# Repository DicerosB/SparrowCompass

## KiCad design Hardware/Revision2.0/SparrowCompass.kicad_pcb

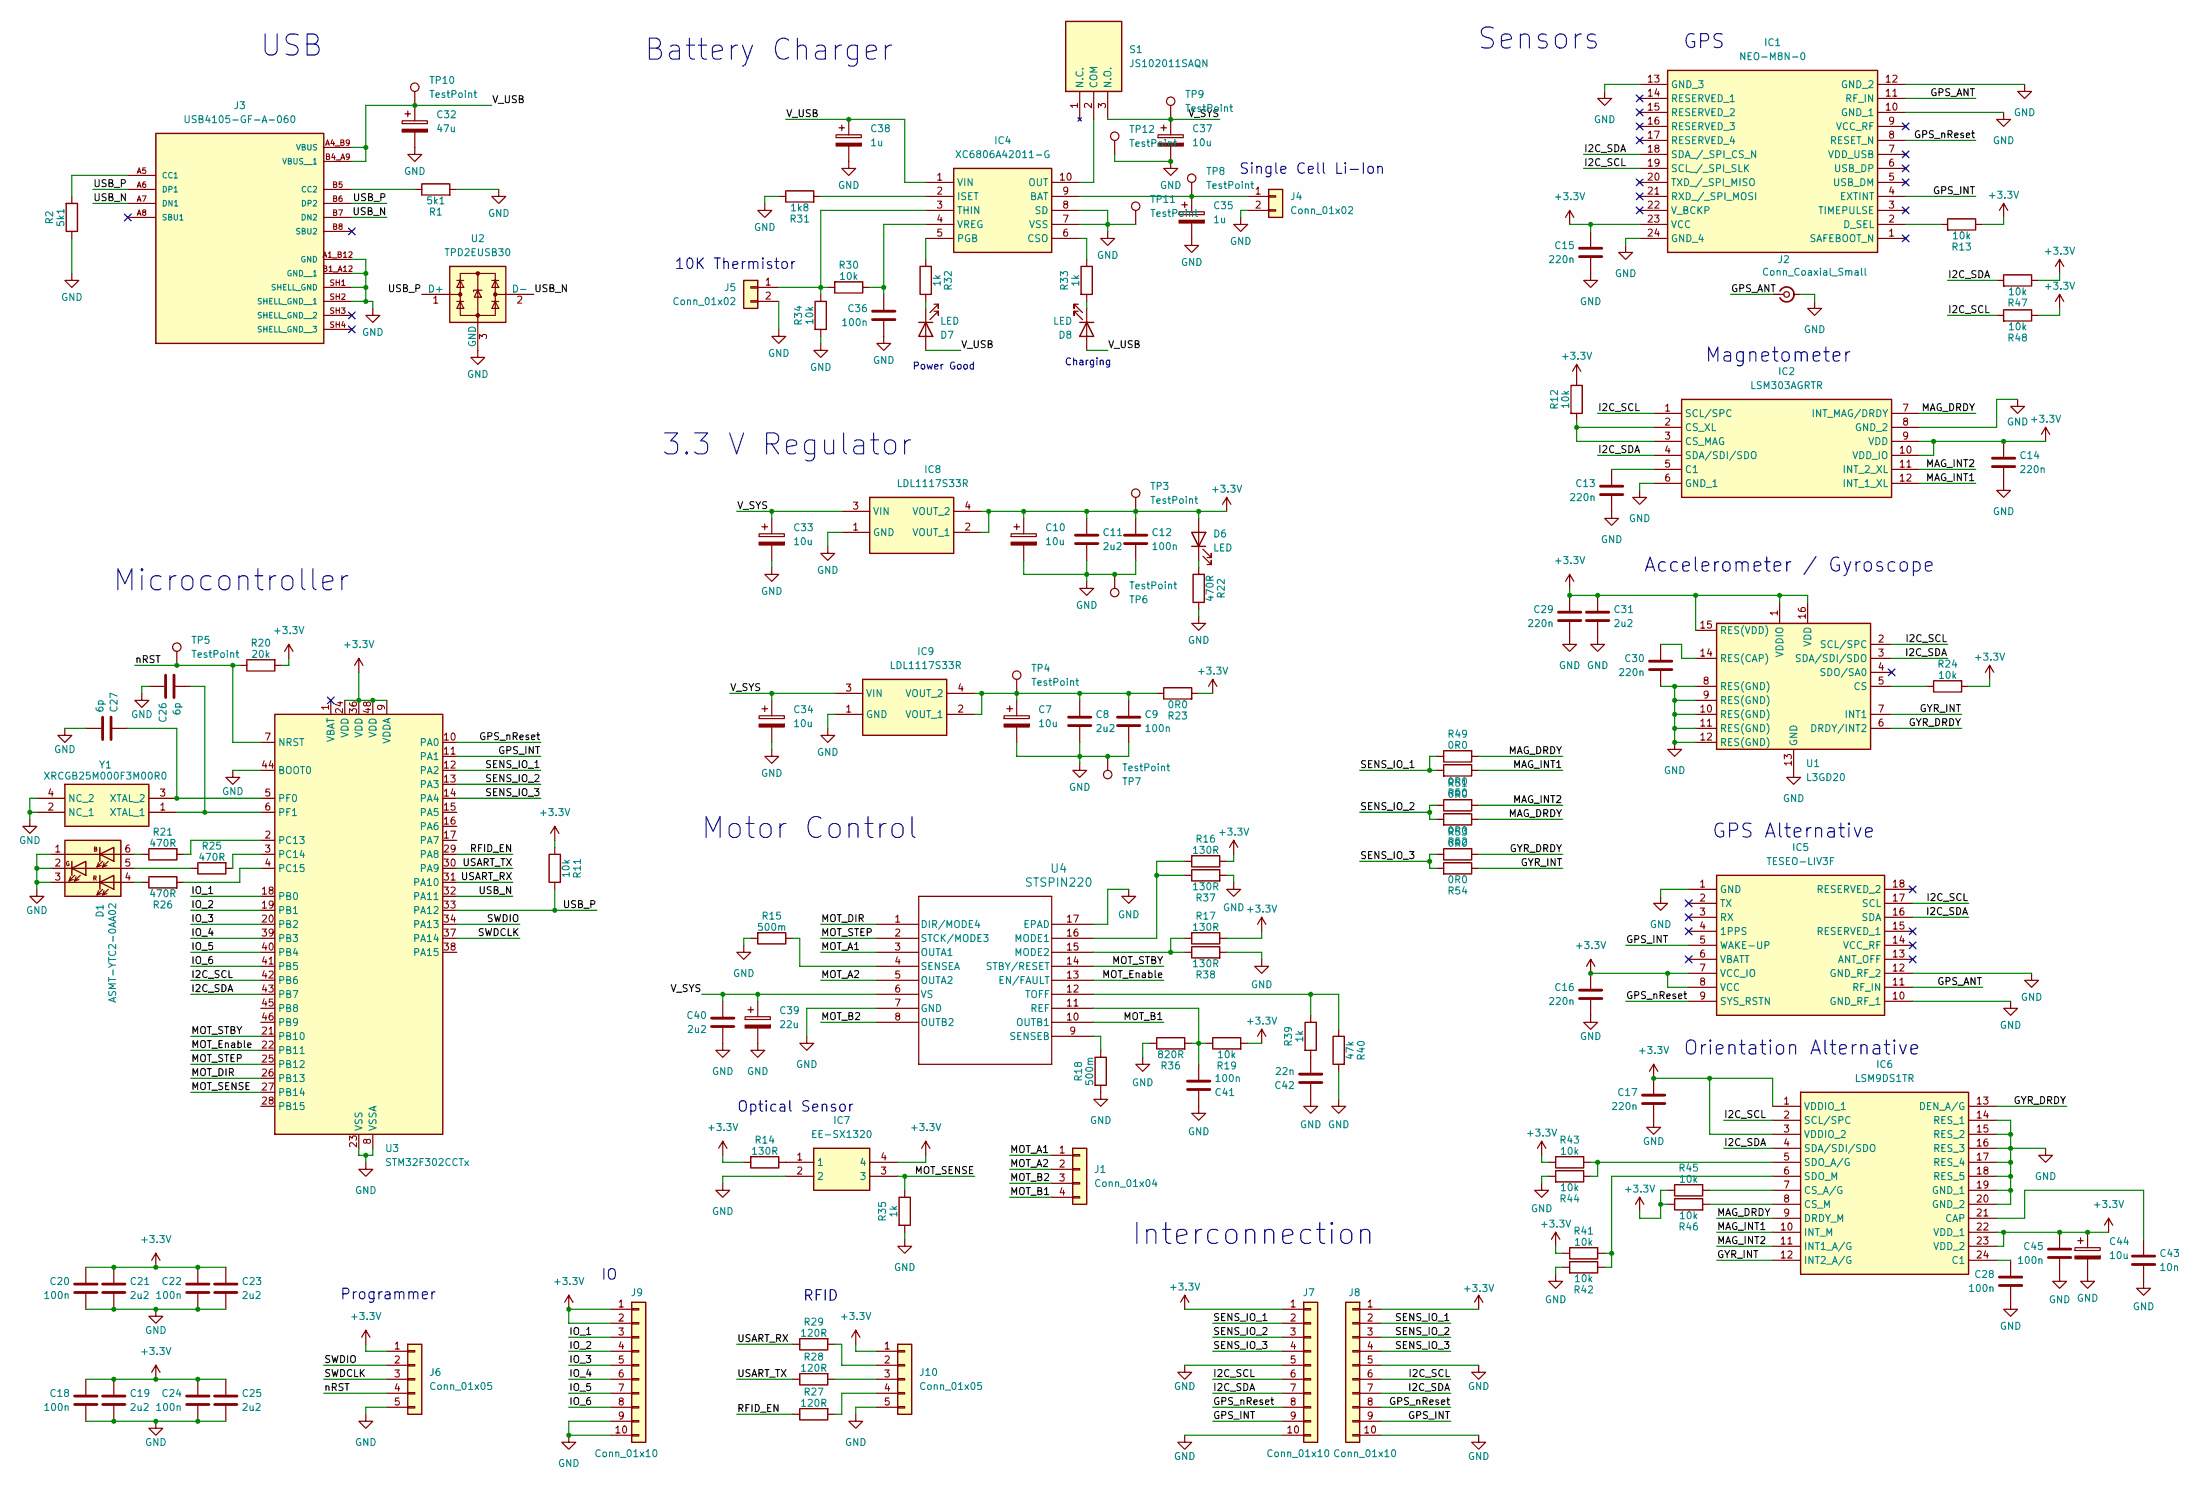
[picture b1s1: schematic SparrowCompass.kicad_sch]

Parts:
C7, C10, C33, C34, C37, C44: 10u; CP_EIA-6032-15_Kemet-U
C8, C11, C19, C21, C23, C25, C31, C40: 2u2; C_0603_1608Metric
C9, C12, C18, C20, C22, C24, C28, C36, C41, C45: 100n; C_0603_1608Metric
C13, C14, C15, C16, C17, C29, C30: 220n; C_0603_1608Metric
C26, C27: 6p; C_0603_1608Metric
C32: 47u; CP_EIA-6032-15_Kemet-U
C35, C38: 1u; CP_EIA-6032-15_Kemet-U
C39: 22u; CP_EIA-6032-15_Kemet-U
C42: 22n; C_0603_1608Metric
C43: 10n; C_0603_1608Metric
D1: ASMT-YTC2-0AA02; LED_Avago_PLCC6_3x2.8mm
D6, D7, D8: LED; LED_0603_1608Metric
IC1: NEO-M8N-0; NEO-M8T; Mouser Part Number 377-NEO-M8N-0
IC2: LSM303AGRTR; LGA-12; Mouser Part Number 511-LSM303AGRTR
IC4: XC6806A42011-G; XC6806A42011G; Manufacturer_Part_Number XC6806A42011-G
IC5: TESEO-LIV3F; SON110P970X1010X230-18N; Manufacturer_Part_Number TESEO-LIV3F
IC6: LSM9DS1TR; LGA-24L_3X3.5X1MM_; Manufacturer_Part_Number LSM9DS1TR
IC7: EE-SX1320; Mouser Part Number 653-EESX1320
IC8, IC9: LDL1117S33R; SOT230P700X180-4N; Manufacturer_Part_Number LDL1117S33R
J1: Conn_01x04; PinHeader_1x04_P2.54mm_Vertical
J2: Conn_Coaxial_Small; U.FL_Hirose_U.FL-R-SMT-1_Vertical
J3: USB4105-GF-A-060; GCT_USB4105-GF-A-060; PARTREV B3
J4, J5: Conn_01x02; PinHeader_1x02_P2.54mm_Vertical
J6, J10: Conn_01x05; PinHeader_1x05_P2.54mm_Vertical
J7, J8, J9: Conn_01x10; PinHeader_1x10_P1.27mm_Vertical
R1, R2: 5k1; R_0603_1608Metric
R11, R12, R13, R19, R24, R30, R34, R41, R42, R43, R44, R45, R46, R47, R48: 10k; R_0603_1608Metric
R14, R16, R17, R37, R38: 130R; R_0603_1608Metric
R15, R18: 500m; R_0603_1608Metric
R20: 20k; R_0603_1608Metric
R21, R22, R25, R26: 470R; R_0603_1608Metric
R23, R49, R50, R51, R52, R53, R54: 0R0; R_0603_1608Metric
R27, R28, R29: 120R; R_0603_1608Metric
R31: 1k8; R_0603_1608Metric
R32, R33, R35, R39: 1k; R_0603_1608Metric
R36: 820R; R_0603_1608Metric
R40: 47k; R_0603_1608Metric
S1: JS102011SAQN; Manufacturer_Part_Number JS102011SAQN
TP3, TP4, TP5, TP6, TP7, TP8, TP9, TP10, TP11, TP12: TestPoint; TestPoint_THTPad_D1.0mm_Drill0.5mm
U1: L3GD20; LGA-16_4x4mm_P0.65mm_LayoutBorder4x4y
U2: TPD2EUSB30; Texas_DRT-3
U3: STM32F302CCTx; LQFP-48_7x7mm_P0.5mm
U4: STSPIN220; VFQFPN-16_STM
Y1: XRCGB25M000F3M00R0; XRCGB; Mouser Part Number 81-XRCGB25M000F3M0R0

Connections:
+3.3V: C10.1, C11.1, C12.1, C14.1, C15.1, C16.1, C17.1, C18.1, C19.1, C20.1, C21.1, C22.1, C23.1, C24.1, C25.1, C29.1, C31.1, C44.1, C45.1, D6.2 (A), IC1.23 (VCC), IC2.9 (VDD), IC2.10 (VDD_IO), IC5.7 (VCC_IO), IC5.8 (VCC), IC6.1 (VDDIO_1), IC6.3 (VDDIO_2), IC6.22 (VDD_1), IC6.23 (VDD_2), IC7.4, IC8.2 (VOUT_1), IC8.4 (VOUT_2), J6.1, J7.1, J8.1, J9.1, J9.2, J10.1, R11.1, R12.1, R13.1, R14.2, R16.1, R17.1, R19.2, R20.2, R23.2, R24.2, R41.1, R43.1, R45.1, R46.1, R47.1, R48.1, TP3.1 (1_1), U1.1 (VDDIO), U1.15 (RES(VDD)), U1.16 (VDD), U3.9 (VDDA), U3.24 (VDD), U3.36 (VDD), U3.48 (VDD)
/GPS_ANT: IC1.11 (RF_IN), IC5.11 (RF_IN), J2.1 (In)
/GPS_INT: IC1.4 (EXTINT), IC5.5 (WAKE-UP), J7.9, J8.9, U3.11 (PA1)
/GPS_nReset: IC1.8 (RESET_N), IC5.9 (SYS_RSTN), J7.8, J8.8, U3.10 (PA0)
/GYR_DRDY: IC6.13 (DEN_A/G), R53.2, U1.6 (DRDY/INT2)
/GYR_INT: IC6.12 (INT2_A/G), R54.1, U1.7 (INT1)
/I2C_SCL: IC1.19 (SCL_/_SPI_SLK), IC2.1 (SCL/SPC), IC5.17 (SCL), IC6.2 (SCL/SPC), J7.6, J8.6, R48.2, U1.2 (SCL/SPC), U3.42 (PB6)
/I2C_SDA: IC1.18 (SDA_/_SPI_CS_N), IC2.4 (SDA/SDI/SDO), IC5.16 (SDA), IC6.4 (SDA/SDI/SDO), J7.7, J8.7, R47.2, U1.3 (SDA/SDI/SDO), U3.43 (PB7)
/IO_1: J9.3, U3.18 (PB0)
/IO_2: J9.4, U3.19 (PB1)
/IO_3: J9.5, U3.20 (PB2)
/IO_4: J9.6, U3.39 (PB3)
/IO_5: J9.7, U3.40 (PB4)
/IO_6: J9.8, U3.41 (PB5)
/MAG_DRDY: IC2.7 (INT_MAG/DRDY), IC6.9 (DRDY_M), R49.2, R52.1
/MAG_INT1: IC2.12 (INT_1_XL), IC6.10 (INT_M), R50.1
/MAG_INT2: IC2.11 (INT_2_XL), IC6.11 (INT1_A/G), R51.2
/MOT_A1: J1.1, U4.3 (OUTA1)
/MOT_A2: J1.2, U4.5 (OUTA2)
/MOT_B1: J1.4, U4.10 (OUTB1)
/MOT_B2: J1.3, U4.8 (OUTB2)
/MOT_DIR: U3.26 (PB13), U4.1 (DIR/MODE4)
/MOT_Enable: U3.22 (PB11), U4.13 (EN/FAULT)
/MOT_SENSE: IC7.3, R35.1, U3.27 (PB14)
/MOT_STBY: U3.21 (PB10), U4.14 (STBY/RESET)
/MOT_STEP: U3.25 (PB12), U4.2 (STCK/MODE3)
/RFID_EN: R27.1, U3.29 (PA8)
/SENS_IO_1: J7.2, J8.2, R49.1, R50.2, U3.12 (PA2)
/SENS_IO_2: J7.3, J8.3, R51.1, R52.2, U3.13 (PA3)
/SENS_IO_3: J7.4, J8.4, R53.1, R54.2, U3.14 (PA4)
/SWDCLK: J6.3, U3.37 (PA14)
/SWDIO: J6.2, U3.34 (PA13)
/USART_RX: R29.1, U3.31 (PA10)
/USART_TX: R28.1, U3.30 (PA9)
/USB_N: J3.A7 (DN1), J3.B7 (DN2), U2.2 (D-), U3.32 (PA11)
/USB_P: J3.A6 (DP1), J3.B6 (DP2), R11.2, U2.1 (D+), U3.33 (PA12)
/V_SYS: C33.1, C34.1, C37.1, C39.1, C40.1, IC8.3 (VIN), IC9.3 (VIN), S1.3 (N.O.), TP9.1 (1_1), U4.6 (VS)
/V_USB: C32.1, C38.1, D7.2 (A), D8.2 (A), IC4.1 (VIN), J3.A4_B9 (VBUS), J3.B4_A9 (VBUS__1), TP10.1 (1_1)
/nRST: J6.4, R20.1, TP5.1 (1_1), U3.7 (NRST)
GND: C7.2, C8.2, C9.2, C10.2, C11.2, C12.2, C13.2, C14.2, C15.2, C16.2, C17.2, C18.2, C19.2, C20.2, C21.2, C22.2, C23.2, C24.2, C25.2, C26.1, C27.2, C28.2, C29.2, C30.2, C31.2, C32.2, C33.2, C34.2, C35.2, C36.2, C37.2, C38.2, C39.2, C40.2, C41.1, C42.1, C43.2, C44.2, C45.2, D1.1 (KB), D1.2 (KG), D1.3 (KR), IC1.10 (GND_1), IC1.12 (GND_2), IC1.13 (GND_3), IC1.24 (GND_4), IC2.6 (GND_1), IC2.8 (GND_2), IC4.7 (VSS), IC4.8 (SD), IC5.1 (GND), IC5.10 (GND_RF_1), IC5.12 (GND_RF_2), IC6.14 (RES_1), IC6.15 (RES_2), IC6.16 (RES_3), IC6.17 (RES_4), IC6.18 (RES_5), IC6.19 (GND_1), IC6.20 (GND_2), IC7.2, IC8.1 (GND), IC9.1 (GND), J2.2 (Ext), J3.A1_B12 (GND), J3.B1_A12 (GND__1), J3.SH1 (SHELL_GND), J3.SH2 (SHELL_GND__1), J4.2, J5.2, J6.5, J7.5, J7.10, J8.5, J8.10, J9.9, J9.10, J10.5, R1.2, R2.1, R15.2, R18.2, R22.1, R31.1, R34.2, R35.2, R36.1, R37.2, R38.2, R40.2, R42.2, R44.2, TP6.1 (1_1), TP7.1 (1_1), TP11.1 (1_1), TP12.1 (1_1), U1.8 (RES(GND)), U1.9 (RES(GND)), U1.10 (RES(GND)), U1.11 (RES(GND)), U1.12 (RES(GND)), U1.13 (GND), U2.3 (GND), U3.8 (VSSA), U3.23 (VSS), U3.35 (VSS), U3.44 (BOOT0), U3.47 (VSS), U4.7 (GND), U4.17 (EPAD), Y1.2 (NC_1), Y1.4 (NC_2)
unnamed: C42.2, R39.2
unnamed: D1.6 (AB), R21.1
unnamed: D1.5 (AG), R25.1
unnamed: D1.4 (AR), R26.1
unnamed: D6.1 (K), R22.2
unnamed: D7.1 (K), R32.1
unnamed: D8.1 (K), R33.2
unnamed: IC1.2 (D_SEL), R13.2
unnamed: C13.1, IC2.5 (C1)
unnamed: IC2.2 (CS_XL), IC2.3 (CS_MAG), R12.2
unnamed: C35.1, IC4.9 (BAT), J4.1, TP8.1 (1_1)
unnamed: IC4.6 (CSO), R33.1
unnamed: IC4.2 (ISET), R31.2
unnamed: IC4.10 (OUT), S1.2 (COM)
unnamed: IC4.5 (PGB), R32.2
unnamed: IC4.3 (THIN), J5.1, R30.2, R34.1
unnamed: C36.1, IC4.4 (VREG), R30.1
unnamed: C28.1, IC6.24 (C1)
unnamed: C43.1, IC6.21 (CAP)
unnamed: IC6.7 (CS_A/G), R45.2
unnamed: IC6.8 (CS_M), R46.2
unnamed: IC6.5 (SDO_A/G), R43.2, R44.1
unnamed: IC6.6 (SDO_M), R41.2, R42.1
unnamed: IC7.1, R14.1
unnamed: C7.1, C8.1, C9.1, IC9.2 (VOUT_1), IC9.4 (VOUT_2), R23.1, TP4.1 (1_1)
unnamed: J3.A5 (CC1), R2.2
unnamed: J3.B5 (CC2), R1.1
unnamed: J10.2, R29.2
unnamed: J10.3, R28.2
unnamed: J10.4, R27.2
unnamed: R24.1, U1.5 (CS)
unnamed: C30.1, U1.14 (RES(CAP))
unnamed: R21.2, U3.2 (PC13)
unnamed: R25.2, U3.3 (PC14)
unnamed: R26.2, U3.4 (PC15)
unnamed: C27.1, U3.5 (PF0), Y1.3 (XTAL_2)
unnamed: C26.2, U3.6 (PF1), Y1.1 (XTAL_1)
unnamed: R16.2, R37.1, U4.16 (MODE1)
unnamed: R17.2, R38.1, U4.15 (MODE2)
unnamed: C41.2, R19.1, R36.2, U4.11 (REF)
unnamed: R15.1, U4.4 (SENSEA)
unnamed: R18.1, U4.9 (SENSEB)
unnamed: R39.1, R40.1, U4.12 (TOFF)

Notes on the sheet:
RFID
Optical Sensor
Battery Charger
3.3 V Regulator
Sensors
Charging
Single Cell Li-Ion
Orientation Alternative
10K Thermistor
GPS Alternative
Accelerometer / Gyroscope
Programmer
Motor Control
Microcontroller
Interconnection
Power Good
USB
Magnetometer
GPS

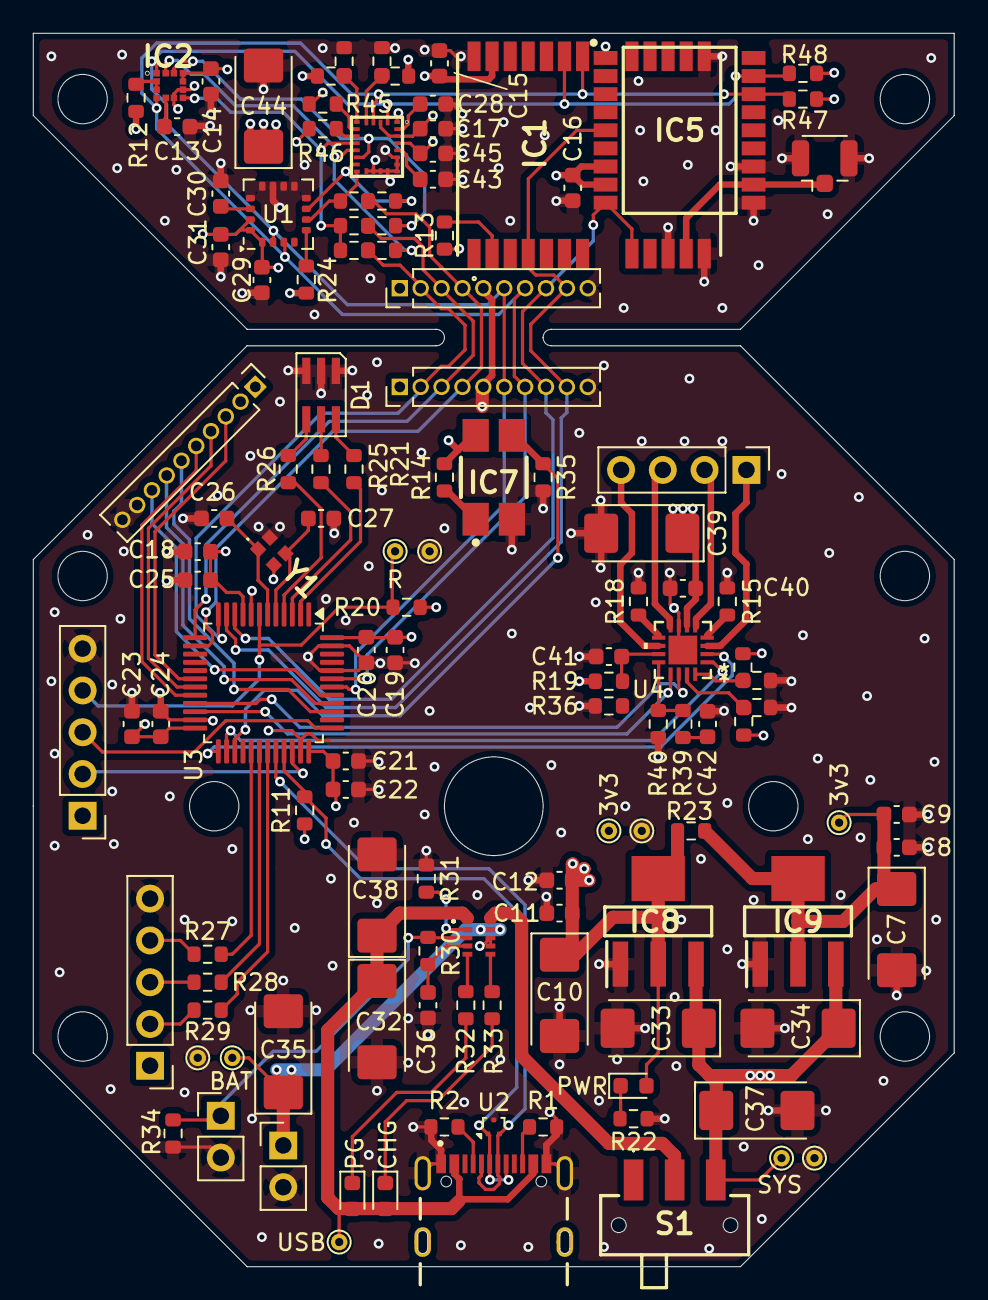
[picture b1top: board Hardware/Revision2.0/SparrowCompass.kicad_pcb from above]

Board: 4 copper layers, 56.0 x 75.0 mm, 123 parts (0 on the bottom side), 83 nets.

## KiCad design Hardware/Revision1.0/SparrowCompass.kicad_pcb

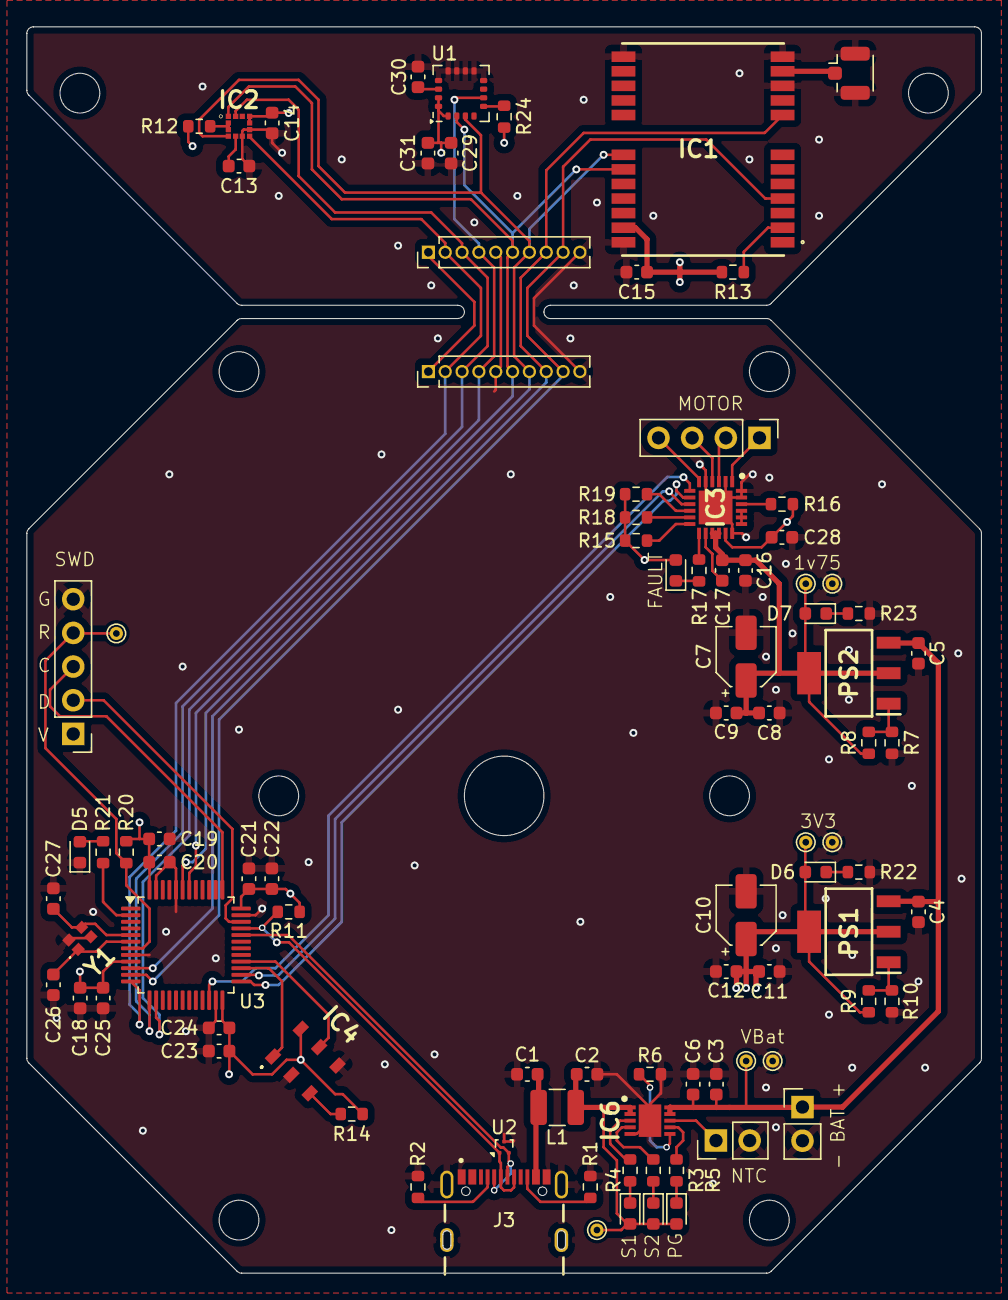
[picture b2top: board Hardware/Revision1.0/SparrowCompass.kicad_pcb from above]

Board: 4 copper layers, 72.0 x 94.0 mm, 90 parts (0 on the bottom side), 60 nets.

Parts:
C1, C2, C3, C6, C8, C11, C16, C19, C21, C23, C25, C31: 2u2; C_0603_1608Metric
C4, C5, C9, C12, C17, C18, C20, C22, C24, C28: 100n; C_0603_1608Metric
C7, C10: 10u; CP_Elec_4x5.3
C13, C14, C15, C29, C30: 220n; C_0603_1608Metric
C26, C27: 6p; C_0603_1608Metric
D1, D2, D3, D4, D5, D6, D7: LED; LED_0603_1608Metric
IC1: NEO-M8N-0; NEO-M8T
IC2: LSM303AGRTR; LGA-12
IC3: DRV8834RGER; QFN50P400X400X100-25N-D
IC4: AEDR-8300-1Q2; AEDR83001Q2
IC6: MCP73833T-AMI_MF; SON50P300X300X100-11N-D
J1: Conn_01x04; PinHeader_1x04_P2.54mm_Vertical
J2: Conn_Coaxial_Small; U.FL_Hirose_U.FL-R-SMT-1_Vertical
J3: USB4105-GF-A-060; GCT_USB4105-GF-A-060
J4, J5: Conn_01x02; PinHeader_1x02_P2.54mm_Vertical
J6: Conn_01x05; PinHeader_1x05_P2.54mm_Vertical
J7, J8: Conn_01x10; PinHeader_1x10_P1.27mm_Vertical
L1: 220R; L_1210_3225Metric
PS1, PS2: ZLDO1117QG33TA; SOT230P700X180-4N
R1, R2: 5k1; R_0603_1608Metric
R3, R4, R5, R14, R17, R21, R22, R23: 470R; R_0603_1608Metric
R6: 1k; R_0603_1608Metric
R7: 80R; R_0603_1608Metric
R8, R9: 200R; R_0603_1608Metric
R10: 330R; R_0603_1608Metric
R11, R12, R13, R15, R16, R18, R19, R24: 10k; R_0603_1608Metric
R20: 20k; R_0603_1608Metric
TP1, TP2, TP3, TP4, TP5, TP6, TP7, TP8: TestPoint; TestPoint_THTPad_D1.0mm_Drill0.5mm
U1: L3GD20; LGA-16_4x4mm_P0.65mm_LayoutBorder4x4y
U2: TPD2EUSB30; Texas_DRT-3
U3: STM32F302CCTx; LQFP-48_7x7mm_P0.5mm
Y1: XRCGB25M000F3M00R0; XRCGB

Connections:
+3.3V: C10.1, C11.1, C12.1, C14.1, C15.1, C18.1, C19.1, C20.1, C21.1, C22.1, C23.1, C24.1, C25.1, C28.1, C29.1, C31.1, D4.2 (A), D6.2 (A), IC1.23 (VCC), IC2.9 (VDD), IC2.10 (VDD_IO), IC3.17 (VINT), IC4.6 (VCC), J6.1, J7.1, J8.1, PS1.2 (VOUT_1), PS1.4 (VOUT_2), R9.2, R11.1, R12.1, R13.1, R14.2, R15.1, R16.1, R18.1, R19.1, R20.1, R24.2, TP3.1, U1.1 (VDDIO), U1.15 (RES(VDD)), U1.16 (VDD), U3.9 (VDDA), U3.24 (VDD), U3.36 (VDD), U3.48 (VDD)
/1V75: C7.1, C8.1, C9.1, C16.1, C17.1, D7.2 (A), IC3.15 (VM_1), IC3.16 (VM_2), PS2.2 (VOUT_1), PS2.4 (VOUT_2), R8.2, TP4.1
/GPS_INT: IC1.4 (EXTINT), J7.9, J8.9, U3.11 (PA1)
/GPS_nReset: IC1.8 (RESET_N), J7.8, J8.8, U3.10 (PA0)
/GYR_DRDY: J7.4, J8.4, U1.6 (DRDY/INT2), U3.14 (PA4)
/I2C_SCL: IC1.19 (SCL_/_SPI_SLK), IC2.1 (SCL/SPC), J7.6, J8.6, U1.2 (SCL/SPC), U3.42 (PB6)
/I2C_SDA: IC1.18 (SDA_/_SPI_CS_N), IC2.4 (SDA/SDI/SDO), J7.7, J8.7, U1.3 (SDA/SDI/SDO), U3.43 (PB7)
/MAG_DRDY: IC2.7 (INT_MAG/DRDY), J7.2, J8.2, U3.12 (PA2)
/MAG_INT1: IC2.12 (INT_1_XL), J7.3, J8.3, U3.13 (PA3)
/MOT_A1: IC3.1 (AOUT_1), J1.1
/MOT_A2: IC3.3 (AOUT_2), J1.2
/MOT_B1: IC3.6 (BOUT_1), J1.4
/MOT_B2: IC3.4 (BOUT_2), J1.3
/MOT_DIR: IC3.9 (DIR_/_BPHASE), U3.26 (PB13)
/MOT_SENS_A: IC4.5 (CH_A), U3.28 (PB15)
/MOT_SENS_B: IC4.1 (CH_B), U3.27 (PB14)
/MOT_STEP: IC3.8 (STEP_/_BENBL), U3.25 (PB12)
/MOT_nEnable: IC3.7 (NENBL_/_AENBL), U3.22 (PB11)
/SWDCLK: J6.3, U3.37 (PA14)
/SWDIO: J6.2, U3.34 (PA13)
/USB_N: J3.A7 (DN1), J3.B7 (DN2), U2.2 (D-), U3.32 (PA11)
/USB_P: J3.A6 (DP1), J3.B6 (DP2), R11.2, U2.1 (D+), U3.33 (PA12)
/V_BAT: C3.1, C4.1, C5.1, C6.1, IC6.9 (VBAT_1), IC6.10 (VBAT_2), J4.1, PS1.3 (VIN), PS2.3 (VIN), TP2.1
/V_USB: C2.1, D1.2 (A), D2.2 (A), D3.2 (A), IC6.1 (VDD_1), IC6.2 (VDD_2), L1.2, TP1.1
/nRST: J6.4, R20.2, TP5.1, U3.7 (NRST)
GND: C1.2, C2.2, C3.2, C4.2, C5.2, C6.2, C7.2, C8.2, C9.2, C10.2, C11.2, C12.2, C13.2, C14.2, C15.2, C16.2, C18.2, C19.2, C20.2, C21.2, C22.2, C23.2, C24.2, C25.2, C26.1, C27.2, C28.2, C29.2, C30.2, C31.2, D5.1 (K), IC1.10 (GND_1), IC1.12 (GND_2), IC1.13 (GND_3), IC1.24 (GND_4), IC2.6 (GND_1), IC2.8 (GND_2), IC3.2 (AISEN), IC3.5 (BISEN), IC3.18 (GND_1), IC3.23 (BDECAY), IC3.24 (ADECAY), IC3.25 (GND_2), IC4.2 (GND), IC4.4 (GND_), IC6.5 (VSS), IC6.11 (EP), J2.2 (Ext), J3.A1_B12 (GND), J3.B1_A12 (GND__1), J3.SH1 (SHELL_GND), J3.SH2 (SHELL_GND__1), J3.SH3 (SHELL_GND__2), J3.SH4 (SHELL_GND__3), J4.2, J5.2, J6.5, J7.5, J7.10, J8.5, J8.10, R1.1, R2.1, R6.2, R7.2, R10.2, R22.1, R23.1, TP6.1, TP7.1, TP8.1, U1.8 (RES(GND)), U1.9 (RES(GND)), U1.10 (RES(GND)), U1.11 (RES(GND)), U1.12 (RES(GND)), U1.13 (GND), U2.3 (GND), U3.8 (VSSA), U3.23 (VSS), U3.35 (VSS), U3.44 (BOOT0), U3.47 (VSS), Y1.2 (NC_1), Y1.4 (NC_2)
unnamed: D1.1 (K), R3.2
unnamed: D2.1 (K), R4.1
unnamed: D3.1 (K), R5.2
unnamed: D4.1 (K), R17.2
unnamed: D5.2 (A), R21.1
unnamed: D6.1 (K), R22.2
unnamed: D7.1 (K), R23.2
unnamed: IC1.2 (D_SEL), R13.2
unnamed: IC1.11 (RF_IN), J2.1 (In)
unnamed: C13.1, IC2.5 (C1)
unnamed: IC2.2 (CS_XL), IC2.3 (CS_MAG), R12.2
unnamed: IC3.19 (AVREF), IC3.20 (BVREF), IC3.21 (VREFO)
unnamed: IC3.12 (CONFIG), R15.2
unnamed: IC3.10 (M0_/_APHASE), R19.2
unnamed: IC3.11 (M1), R18.2
unnamed: IC3.13 (NFAULT), R17.1
unnamed: IC3.22 (NSLEEP), R16.2
unnamed: C17.2, IC3.14 (VCP)
unnamed: IC4.3 (VLED), R14.1
unnamed: IC6.6 (PROG), R6.1
unnamed: IC6.3 (STAT1), R3.1
unnamed: IC6.4 (STAT2), R4.2
unnamed: IC6.8 (THERM), J5.1
unnamed: IC6.7 (~PG(TE)), R5.1
unnamed: J3.A5 (CC1), R2.2
unnamed: J3.B5 (CC2), R1.2
unnamed: C1.1, J3.A4_B9 (VBUS), J3.B4_A9 (VBUS__1), L1.1
unnamed: PS1.1 (ADJ), R9.1, R10.1
unnamed: PS2.1 (ADJ), R7.1, R8.1
unnamed: R24.1, U1.5 (CS)
unnamed: C30.1, U1.14 (RES(CAP))
unnamed: R21.2, U3.2 (PC13)
unnamed: C27.1, U3.5 (PF0), Y1.3 (XTAL_2)
unnamed: C26.2, U3.6 (PF1), Y1.1 (XTAL_1)

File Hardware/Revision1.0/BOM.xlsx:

Reference | Qty | Value | DNP | Footprint | Datasheet | Cost | Link | total
C1;C2;C3;C6;C8;C11;C16;C19;C21;C23;C25;C31 | 12 | 2u2 |  | Capacitor_SMD:C_0603_1608Metric | ~ | 0.09 | https://www.mouser.de/ProductDetail/Murata-Electronics/GRM18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 | 1.08
C4;C5;C9;C12;C17;C18;C20;C22;C24;C28 | 10 | 100n |  | Capacitor_SMD:C_0603_1608Metric | ~ | 0.09 | https://www.mouser.de/ProductDetail/KEMET/C0603C104Z4VACTU?q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 | 0.89999999999999991
C7;C10 | 2 | 10u |  | Capacitor_SMD:CP_Elec_4x5.3 | ~ | 0.05 | https://www.mouser.de/ProductDetail/Knowles-Illinois-Capacit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 | 0.1
C13;C14;C15;C29;C30 | 5 | 220n |  | Capacitor_SMD:C_0603_1608Metric | ~ | 0.09 | https://www.mouser.de/ProductDetail/Murata-Electronics/GRM18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 | 0.44999999999999996
C26;C27 | 2 | 6p |  | Capacitor_SMD:C_0603_1608Metric | ~ | 0.09 | https://www.mouser.de/ProductDetail/Murata-Electronics/GCM18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 | 0.18
D1;D2;D3;D4;D5;D6;D7 | 7 | LED |  | LED_SMD:LED_0603_1608Metric | ~ | 0.15 | https://www.mouser.de/ProductDetail/Wurth-Elektronik/150060B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 | 1.05
IC1 | 1 | NEO-M8N-0 |  | NEO-M8N-0:NEO-M8T | https://www.u-blox.com/sites/default/files/NEO-M8-FW3_DataSh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 | 27.09 | https://www.mouser.de/ProductDetail/u-blox/NEO-M8N-0?qs=zW32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 | 27.09
IC2 | 1 | LSM303AGRTR |  | LSM303AGRTR:LGA-12 | http://www.st.com/content/ccc/resource/technical/document/da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 | 4 | https://www.mouser.de/ProductDetail/STMicroelectronics/LSM30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 | 4
IC3 | 1 | DRV8834RGER |  | DRV8834RGER:QFN50P400X400X100-25N-D | http://www.ti.com/lit/gpn/drv8834 | 2.35 | https://www.mouser.de/ProductDetail/Texas-Instruments/DRV883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 | 2.35
IC4 | 1 | AEDR-8300-1Q2 |  | AEDR-8300-1Q2:AEDR83001Q2 | https://www.digikey.ph/en/products/detail/broadcom-limited/A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 | 8.31 | https://www.mouser.de/ProductDetail/Broadcom-Avago/AEDR-8300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 | 8.31
IC6 | 1 | MCP73833T-AMI_MF |  | MCP73833T-AMI_MF:SON50P300X300X100-11N-D | https://datasheet.datasheetarchive.com/originals/distributor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 | 0.98 | https://www.mouser.de/ProductDetail/Microchip-Technology/MCP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 | 0.98
J2 | 1 | Conn_Coaxial_Small |  | Connector_Coaxial:U.FL_Hirose_U.FL-R-SMT-1_Vertical | ~ | 1.25 | https://www.mouser.de/ProductDetail/Hirose-Connector/U.FL-R-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 | 1.25
J3 | 1 | USB4105-GF-A-060 |  | USB4105_GF_A_060:GCT_USB4105-GF-A-060 |  | 0.67 | https://www.mouser.de/ProductDetail/GCT/USB4105-GF-A-060?qs=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 | 0.67
L1 | 1 | 220R |  | Inductor_SMD:L_1210_3225Metric | ~ | 3.06 | https://www.mouser.de/ProductDetail/Wurth-Elektronik/7687709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 | 3.06
PS1;PS2 | 2 | ZLDO1117QG33TA |  | ZLDO1117QG33TA:SOT230P700X180-4N | https://www.diodes.com//assets/Datasheets/products_inactive_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 | 0.46 | https://www.mouser.de/ProductDetail/Diodes-Incorporated/ZLDO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 | 0.92
R1;R2 | 2 | 5k1 |  | Resistor_SMD:R_0603_1608Metric | ~ | 0.09 | https://www.mouser.de/ProductDetail/Vishay/CRCW06035K11FKEA?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 | 0.18
R3;R4;R5;R14;R17;R21;R22;R23 | 8 | 470R |  | Resistor_SMD:R_0603_1608Metric | ~ | 0.09 |  | 0.72
R6 | 1 | 1k |  | Resistor_SMD:R_0603_1608Metric | ~ | 0.09 |  | 0.09
R7 | 1 | 80R |  | Resistor_SMD:R_0603_1608Metric | ~ | 0.09 |  | 0.09
R8;R9 | 2 | 200R |  | Resistor_SMD:R_0603_1608Metric | ~ | 0.09 |  | 0.18
R10 | 1 | 330R |  | Resistor_SMD:R_0603_1608Metric | ~ | 0.09 |  | 0.09
R11;R12;R13;R15;R16;R18;R19;R24 | 8 | 10k |  | Resistor_SMD:R_0603_1608Metric | ~ | 0.09 |  | 0.72
R20 | 1 | 20k |  | Resistor_SMD:R_0603_1608Metric | ~ | 0.09 |  | 0.09
U1 | 1 | L3GD20 |  | Package_LGA:LGA-16_4x4mm_P0.65mm_LayoutBorder4x4y | http://www.st.com/st-web-ui/static/active/en/resource/techni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 | 14.03 | https://www.mouser.de/ProductDetail/STMicroelectronics/A3G42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 | 14.03
U2 | 1 | TPD2EUSB30 |  | Package_TO_SOT_SMD:Texas_DRT-3 | http://www.ti.com/lit/ds/symlink/tpd2eusb30a.pdf | 0.48 | https://www.mouser.de/ProductDetail/Texas-Instruments/TPD2EU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 | 0.48
U3 | 1 | STM32F302CCTx |  | Package_QFP:LQFP-48_7x7mm_P0.5mm | https://www.st.com/resource/en/datasheet/stm32f302cc.pdf | 5.23 | https://www.mouser.de/ProductDetail/STMicroelectronics/STM32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 | 5.23
Y1 | 1 | XRCGB25M000F3M00R0 |  | XRCGB25M000F3M00R0:XRCGB | https://www.murata.com/products/productdata/8801059864606/SP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 | 0.215 | https://www.mouser.de/ProductDetail/Murata-Electronics/XRCGB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 | 0.215
 |  | RFID Module |  |  |  | 5.67 | https://funduinoshop.com/elektronische-module/wireless-iot/r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 | 5.67
 |  | GPS Antenna |  |  |  | 3.15 | https://www.mouser.de/ProductDetail/KYOCERA-AVX/9000440F0-AA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 | 3.15
 |  | Nema-Flat Stepper Motor |  |  |  | 22.5 | https://www.reichelt.de/de/de/shop/produkt/schrittmotor_nema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 | 22.5
 |  |  |  |  |  |  | + PCB | 14
 |  |  |  |  |  |  | Summe: | 119.82500000000003

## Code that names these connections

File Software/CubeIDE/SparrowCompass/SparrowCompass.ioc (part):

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Mcu.Name=STM32L151CCTx
Mcu.Package=LQFP48
Mcu.UserName=STM32L151CCTx
PA0-WKUP1.GPIOParameters=GPIO_Label
PA0-WKUP1.GPIO_Label=GPS_nReset
PA0-WKUP1.Signal=GPIO_Output
PA1.GPIOParameters=GPIO_Label
PA1.GPIO_Label=GPS_INT
PA1.Signal=GPXTI1
PA10.Mode=Asynchronous
PA10.Signal=USART1_RX
PA11.Mode=Device
PA11.Signal=USB_DM
PA12.Mode=Device
PA12.Signal=USB_DP
PA13.Mode=Serial_Wire
PA13.Signal=SYS_JTMS-SWDIO
PA14.Mode=Serial_Wire
PA14.Signal=SYS_JTCK-SWCLK
PA2.GPIOParameters=GPIO_Label
PA2.GPIO_Label=MAG_DRDY
PA2.Signal=GPXTI2
PA3.GPIOParameters=GPIO_Label
PA3.GPIO_Label=MAG_INT1
PA3.Signal=GPXTI3
PA4.GPIOParameters=GPIO_Label
PA4.GPIO_Label=GYR_DRDY
PA4.Signal=GPXTI4
PA9.Mode=Asynchronous
PA9.Signal=USART1_TX
PB11.GPIOParameters=GPIO_Label
PB11.GPIO_Label=MOT_nEnable
PB11.Signal=GPIO_Output
PB12.GPIOParameters=GPIO_Label
PB12.GPIO_Label=MOT_STEP
PB12.Signal=S_TIM10_CH1
PB13.GPIOParameters=GPIO_Speed,GPIO_Label
PB13.GPIO_Label=MOT_DIR
PB13.GPIO_Speed=GPIO_SPEED_FREQ_HIGH
PB13.Signal=GPIO_Output
PB14.GPIOParameters=GPIO_Label
PB14.GPIO_Label=MOT_SENS_B
PB14.Signal=GPXTI14
PB15.GPIOParameters=GPIO_Label
PB15.GPIO_Label=MOT_SENS_A
PB15.Signal=GPXTI15
PB6.Mode=I2C
PB6.Signal=I2C1_SCL
PB7.Mode=I2C
PB7.Signal=I2C1_SDA
PC13-WKUP2.GPIOParameters=GPIO_PuPd,GPIO_Label,GPIO_ModeDefaultOutputPP
PC13-WKUP2.GPIO_Label=DEBUG_LED
PC13-WKUP2.GPIO_ModeDefaultOutputPP=GPIO_MODE_OUTPUT_PP
PC13-WKUP2.GPIO_PuPd=GPIO_NOPULL
PC13-WKUP2.Signal=GPIO_Output
PH0-OSC_IN.Mode=HSE-External-Oscillator
PH0-OSC_IN.Signal=RCC_OSC_IN
PH1-OSC_OUT.Mode=HSE-External-Oscillator
PH1-OSC_OUT.Signal=RCC_OSC_OUT
RCC.HSE_VALUE=16000000
RCC.SYSCLKFreq_VALUE=16000000
RCC.SYSCLKSource=RCC_SYSCLKSOURCE_HSE
board=custom

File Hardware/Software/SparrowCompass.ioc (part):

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Mcu.Name=STM32F302C(B-C)Tx
Mcu.Package=LQFP48
Mcu.UserName=STM32F302CCTx
PA0.GPIOParameters=GPIO_Label
PA0.GPIO_Label=GPS_nEnable
PA0.Signal=GPIO_Output
PA1.GPIOParameters=GPIO_Label
PA1.GPIO_Label=GPS_INT
PA1.Signal=GPIO_Input
PA11.Mode=Device
PA11.Signal=USB_DM
PA12.Mode=Device
PA12.Signal=USB_DP
PA13.Mode=Serial_Wire
PA13.Signal=SYS_JTMS-SWDIO
PA14.Mode=Serial_Wire
PA14.Signal=SYS_JTCK-SWCLK
PA2.GPIOParameters=GPIO_Label
PA2.GPIO_Label=MAG_DRDY
PA2.Signal=GPIO_Input
PA3.GPIOParameters=GPIO_Label
PA3.GPIO_Label=MAG_INT1
PA3.Signal=GPIO_Input
PA4.GPIOParameters=GPIO_Label
PA4.GPIO_Label=GYR_DRDY
PA4.Signal=GPIO_Input
PB11.GPIOParameters=GPIO_Label
PB11.GPIO_Label=MOT_nEnable
PB11.Signal=GPIO_Output
PB12.GPIOParameters=GPIO_Label
PB12.GPIO_Label=MOT_STEP
PB12.Signal=GPIO_Output
PB13.GPIOParameters=GPIO_Label
PB13.GPIO_Label=MOT_DIR
PB13.Signal=GPIO_Output
PB6.Mode=I2C
PB6.Signal=I2C1_SCL
PB7.Mode=I2C
PB7.Signal=I2C1_SDA
PC14-OSC32_IN.GPIOParameters=GPIO_Label
PC14-OSC32_IN.GPIO_Label=DEBUG_LED
PC14-OSC32_IN.Signal=GPIO_Output
PF0-OSC_IN.Mode=HSE-External-Oscillator
PF0-OSC_IN.Signal=RCC_OSC_IN
PF1-OSC_OUT.Mode=HSE-External-Oscillator
PF1-OSC_OUT.Signal=RCC_OSC_OUT
RCC.HSEPLLFreq_Value=16000000
RCC.HSE_VALUE=16000000
RCC.SYSCLKFreq_VALUE=48000000
RCC.SYSCLKSourceVirtual=RCC_SYSCLKSOURCE_PLLCLK
board=custom

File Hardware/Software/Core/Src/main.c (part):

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  HAL_GPIO_WritePin(GPS_nEnable_GPIO_Port, GPS_nEnable_Pin, GPIO_PIN_RESET);

  /*Configure GPIO pin Output Level */
  HAL_GPIO_WritePin(GPIOB, MOT_nEnable_Pin|MOT_STEP_Pin|MOT_DIR_Pin, GPIO_PIN_RESET);

  /*Configure GPIO pins : PC13 PC15 */
  GPIO_InitStruct.Pin = GPIO_PIN_13|GPIO_PIN_15;
  GPIO_InitStruct.Mode = GPIO_MODE_ANALOG;
  GPIO_InitStruct.Pull = GPIO_NOPULL;
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  GPIO_InitStruct.Speed = GPIO_SPEED_FREQ_LOW;
  HAL_GPIO_Init(GPS_nEnable_GPIO_Port, &GPIO_InitStruct);

  /*Configure GPIO pins : GPS_INT_Pin MAG_DRDY_Pin MAG_INT1_Pin GYR_DRDY_Pin */
  GPIO_InitStruct.Pin = GPS_INT_Pin|MAG_DRDY_Pin|MAG_INT1_Pin|GYR_DRDY_Pin;
  GPIO_InitStruct.Mode = GPIO_MODE_INPUT;
  GPIO_InitStruct.Pull = GPIO_NOPULL;
  HAL_GPIO_Init(GPIOA, &GPIO_InitStruct);

  /*Configure GPIO pins : PA5 PA6 PA7 PA8
                           PA9 PA10 PA15 */
  GPIO_InitStruct.Pin = GPIO_PIN_5|GPIO_PIN_6|GPIO_PIN_7|GPIO_PIN_8
                          |GPIO_PIN_9|GPIO_PIN_10|GPIO_PIN_15;
  GPIO_InitStruct.Mode = GPIO_MODE_ANALOG;
  GPIO_InitStruct.Pull = GPIO_NOPULL;
  HAL_GPIO_Init(GPIOA, &GPIO_InitStruct);

  /*Configure GPIO pins : PB0 PB1 PB2 PB10
                           PB14 PB15 PB3 PB4
                           PB5 PB8 PB9 */
  GPIO_InitStruct.Pin = GPIO_PIN_0|GPIO_PIN_1|GPIO_PIN_2|GPIO_PIN_10
                          |GPIO_PIN_14|GPIO_PIN_15|GPIO_PIN_3|GPIO_PIN_4
                          |GPIO_PIN_5|GPIO_PIN_8|GPIO_PIN_9;
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  GPIO_InitStruct.Pull = GPIO_NOPULL;
  HAL_GPIO_Init(GPIOB, &GPIO_InitStruct);

  /*Configure GPIO pins : MOT_nEnable_Pin MOT_STEP_Pin MOT_DIR_Pin */
  GPIO_InitStruct.Pin = MOT_nEnable_Pin|MOT_STEP_Pin|MOT_DIR_Pin;
  GPIO_InitStruct.Mode = GPIO_MODE_OUTPUT_PP;
  GPIO_InitStruct.Pull = GPIO_NOPULL;
  GPIO_InitStruct.Speed = GPIO_SPEED_FREQ_LOW;
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
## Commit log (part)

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2025-11-19 added PCB-Design
2025-11-21 added bootloader project
2025-11-22 ENH: enabled usb communication and rerouted printf
2025-11-22 ENH: Implementing bootloader entry
2025-11-26 WIP: Motor control
2025-11-29 added Rev 2 Hardware
2025-12-01 init ardiono library
2025-12-04 FIX: CubeIDE project files
2025-12-04 WIP: project files
2025-12-05 WIP bootloader DFU implementation
2025-12-06 WIP Bootloader mess
2025-12-09 Improved Bootloader switching
2025-12-12 ENH: Added Aduino library and board structure
2025-12-12 DOC: Arduino library installation
2025-12-13 FIX Board manager defines
2025-12-14 ENH: USB CDC
2025-12-14 FIX: Linker Script, no debugging via SWD works
2025-12-16 First working baseline
2025-12-16 FIX: syntax error
2025-12-17 ENH: increased dfu transfer buffer size
2025-12-17 MTN: doc
2025-12-17 DOC: added Datasheets
2025-12-21 removing hardwaresetup.cpp
2025-12-22 creating module files
2025-12-24 WIP: magnetometer i2c object
2025-12-24 FIX: i2c reference in module
2025-12-25 Testcommit
2025-12-30 typo in doc
2026-01-04 FIX: example script
2026-01-07 FIX: wrong system clock speed
2026-01-07 MNT: Added Todo
2026-01-09 WIP: timer PWM
2026-02-21 WIP: motor Timer
2026-02-22 FIX Motor initialisiation
2026-02-23 WIP Smooth Motor
2026-02-25 ENH constant motor acceleration
2026-04-10 FIX: Interrupt Object Access
2026-04-11 FIX Motor Interrupt
2026-04-12 WIP: additional timer for acceleration control
2026-04-26 WIP: Motor rewrote control concept
2026-04-26 FIX: smaller bugs, ENH more commands, motor debug via serial
2026-04-29 FIX preprocessor bugs
2026-05-11 WIP: new hardware revision. WIP: motor debug
2026-05-22 ENH: Hardware v2
2026-05-22 WIP Magnetometer
2026-05-27 ENH: Magnetometer, Plotting function
2026-06-11 Gerber export

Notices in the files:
Hardware/Software/Core/Src/main.c:
Copyright (c) 2025 STMicroelectronics.
All rights reserved.
This software is licensed under terms that can be found in the LICENSE file
